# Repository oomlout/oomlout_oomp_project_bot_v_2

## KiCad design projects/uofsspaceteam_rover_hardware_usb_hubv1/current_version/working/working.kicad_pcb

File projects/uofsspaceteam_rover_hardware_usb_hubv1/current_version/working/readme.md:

# rover_hardware
 
## summary 
* id: uofsspaceteam_rover_hardware_usb_hubv1
* user: uofsspaceteam
* name: rover_hardware
* board: usb_hubv1
* repo: https://github.com/UofSSpaceTeam/rover-hardware
* src_file_repo_kicad_pcb: Projects/Power Distribution/TUSB2077A_test_hub/usb_hub.kicad_pcb
* src_file_repo_kicad_pcb_link: https://github.com/UofSSpaceTeam/rover-hardware/tree/master/Projects/Power Distribution/TUSB2077A_test_hub/usb_hub.kicad_pcb
* src_file_repo_kicad_sch: Projects/Power Distribution/DriveController/DriveControllerPower.kicad_sch
* src_file_repo_kicad_sch_link: https://github.com/UofSSpaceTeam/rover-hardware/tree/master/Projects/Power Distribution/DriveController/DriveControllerPower.kicad_sch
* src_file_repo_brd: Projects/Communication/KiCad_USB/modified_eagle_files/RH025.1.brd
* src_file_repo_brd_link: https://github.com/UofSSpaceTeam/rover-hardware/tree/master/Projects/Communication/KiCad_USB/modified_eagle_files/RH025.1.brd
* src_file_repo_sch: Projects/Power Distribution/TUSB2077A_test_hub/usb_hub.sch
* src_file_repo_sch_link: https://github.com/UofSSpaceTeam/rover-hardware/tree/master/Projects/Power Distribution/TUSB2077A_test_hub/usb_hub.sch
* full details link: https://github.com/oomlout/oomlout_oomp_project_bot_v_2/tree/main/projects/uofsspaceteam_rover_hardware_usb_hubv1/current_version/working

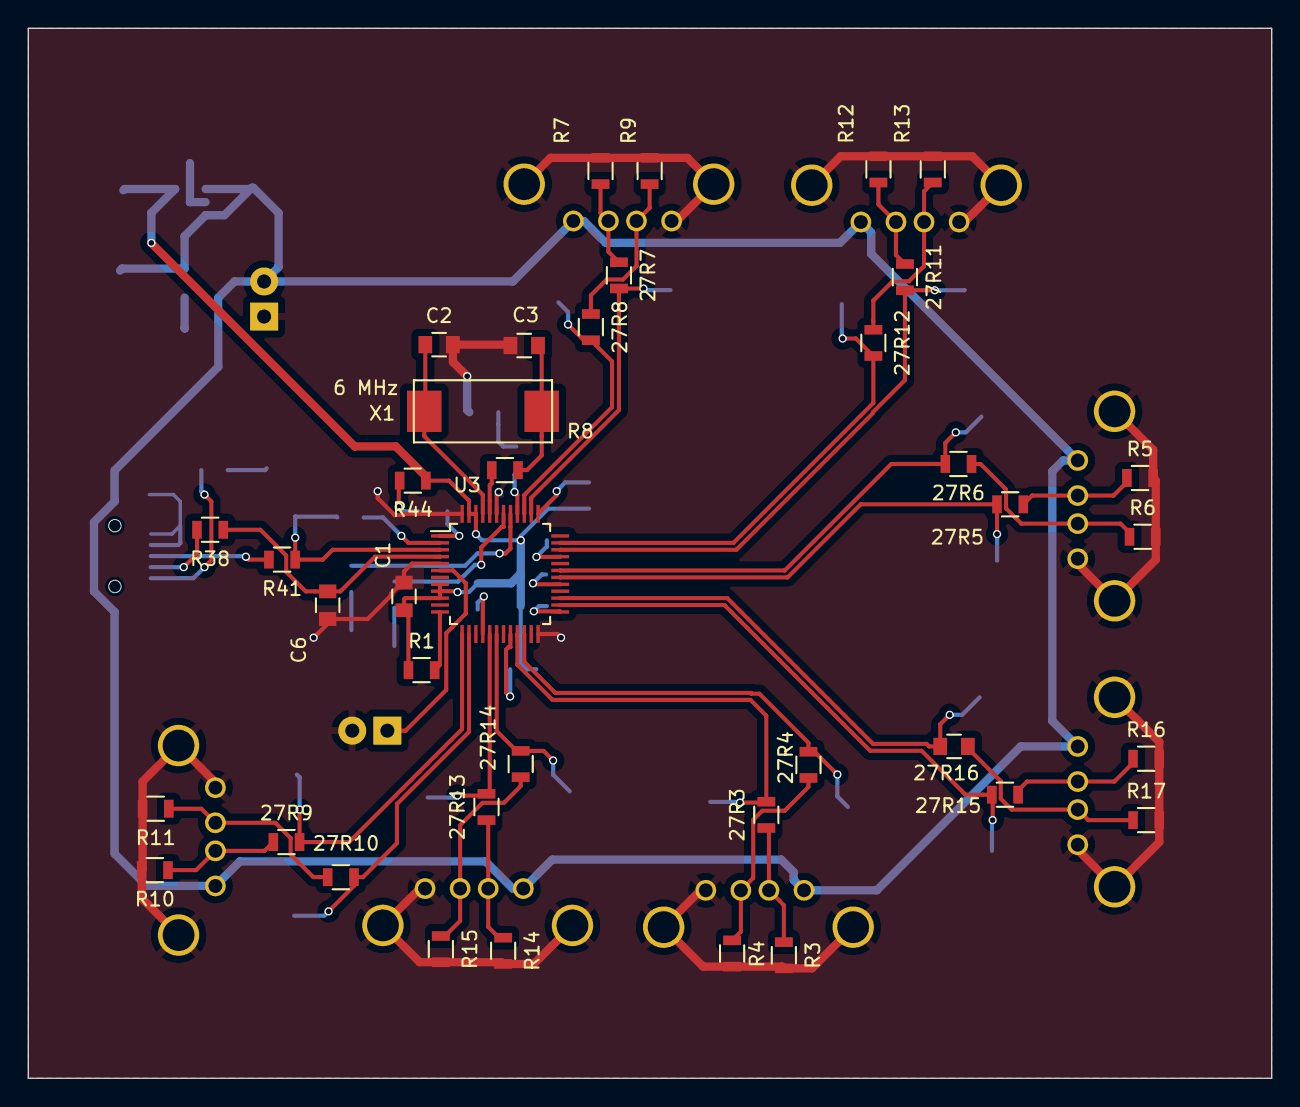
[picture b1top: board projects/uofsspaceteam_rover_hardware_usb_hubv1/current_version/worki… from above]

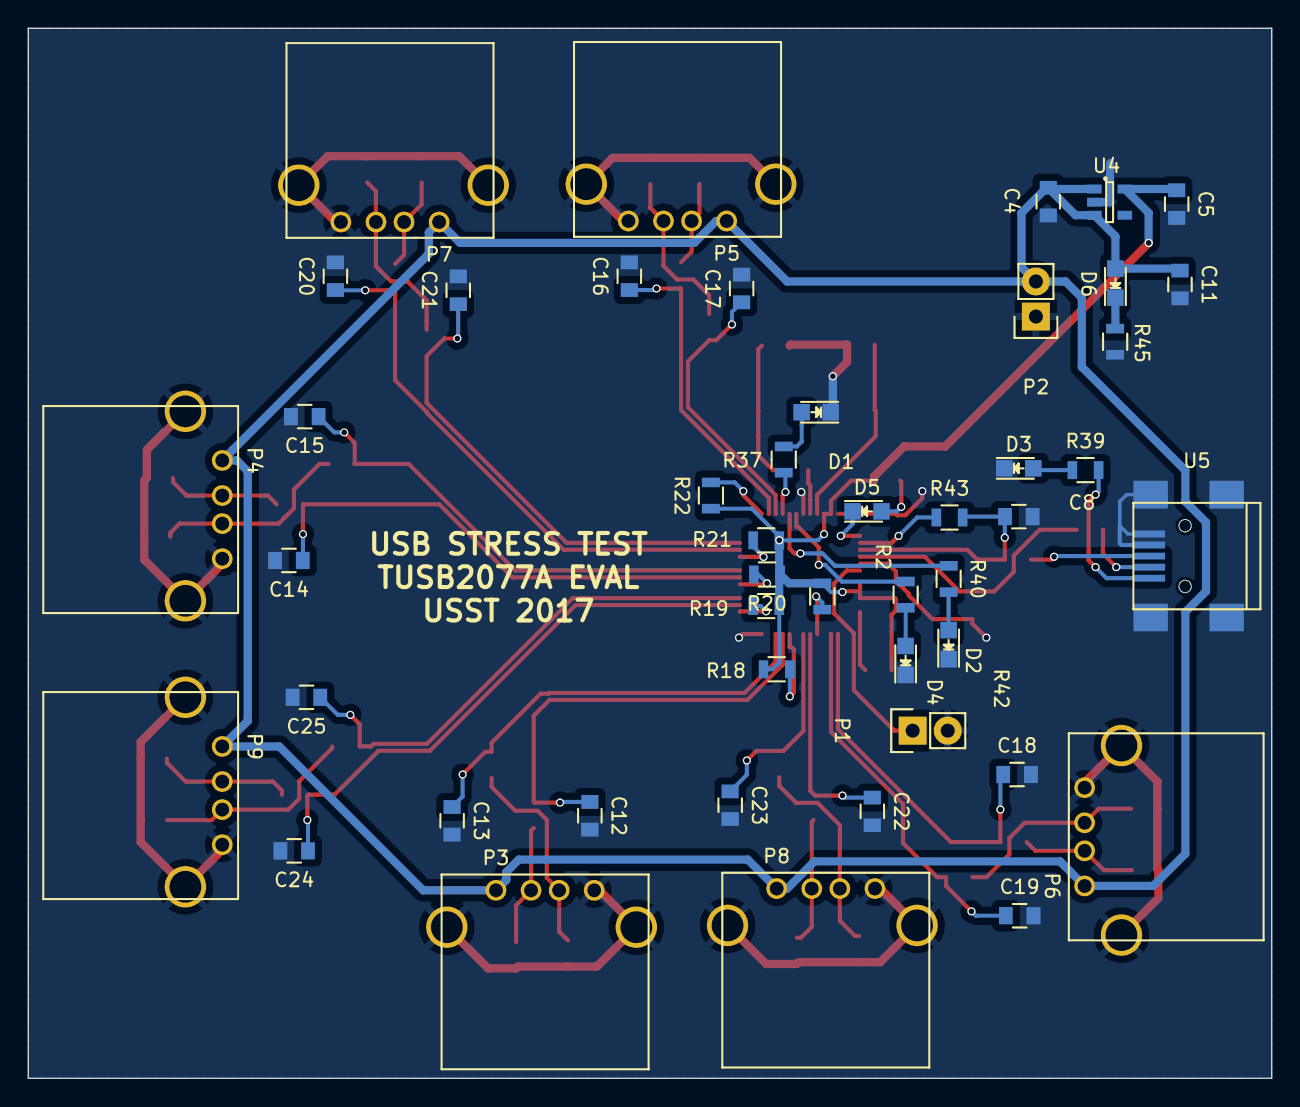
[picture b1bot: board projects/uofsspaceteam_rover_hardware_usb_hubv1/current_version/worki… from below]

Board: 2 copper layers, 90.0 x 76.0 mm, 86 parts (47 on the bottom side), 58 nets.

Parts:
27R3, 27R4, 27R5, 27R6, 27R7, 27R8, 27R9, 27R10, 27R11, 27R12, 27R13, 27R14, 27R15: 27R; R_0805
27R16: 27R; C_0805
C1: 0.1uF; C_0805
C2, C3: 33pF; C_0805
C4: 1uF; C_0805
C5, C11: 10uF; C_0805
C6, C8, C12, C13, C14, C15, C16, C17, C18, C19, C20, C21, C22, C23, C24, C25: 22pF; C_0805
D1, D2, D3, D4, D5, D6: LED; LED_0805
P1: CONN_01X02; Pin_Header_Straight_1x02
P2: CONN_2; Pin_Header_Straight_1x02
P3, P4, P5, P6, P7, P8, P9: USB_A
R1, R2, R3, R4, R5, R6, R7, R9, R10, R11, R12, R13, R14, R15, R16, R17, R18, R19, R20, R21, R22: 15k; R_0805
R8, R43: 1.5k; R_0805
R37, R39, R40, R42, R44, R45: 1k; R_0805
R38, R41: 30; R_0805
U3: TUSB2077A; TQFP-48_7x7mm_Pitch0.5mm
U4: TPS76333; SOT-23-5
U5: USB_A_MALE; USB_Mini-B
X1: 6 MHz; FOX6MHZ

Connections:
+3.3V: C1.1, C5.1, R1.1, R2.1, R18.1, R19.1, R20.1, R21.1, R22.1, R44.1, U3.8, U3.9, U3.10, U3.46, U3.47, U4.5
D0_N: C6.1, R38.1, U3.4
D0_P: C8.1, R41.1, R43.2, U3.3
D1_N: 27R9.2, C18.1, U3.13
D1_P: 27R10.2, C19.1, U3.14
D2_N: 27R13.2, C22.1, U3.17
D2_P: 27R14.2, C23.1, U3.18
D3_N: 27R3.2, C12.1, U3.21
D3_P: 27R4.2, C13.1, U3.22
D4_N: 27R15.2, C24.1, U3.26
D4_P: 27R16.2, C25.1, U3.27
D5_N: 27R5.2, C14.1, U3.30
D5_P: 27R6.2, C15.1, U3.31
D6_N: 27R11.2, C20.1, U3.34
D6_P: 27R12.2, C21.1, U3.35
D7_N: 27R7.2, C16.1, U3.38
D7_P: 27R8.2, C17.1, U3.39
DP0PUR: R43.1, U3.2
GND: C1.2, C2.2, C3.2, C4.2, C5.2, C6.2, C8.2, C11.2, C12.2, C13.2, C14.2, C15.2, C16.2, C17.2, C18.2, C19.2, C20.2, C21.2, C22.2, C23.2, C24.2, C25.2, D1.1, D2.1, D3.1, D4.1, P1.2, P2.1, P3.4, P3.5, P4.4, P4.5, P5.4, P5.5, P6.4, P6.5, P7.4, P7.5, P8.4, P8.5, P9.4, P9.5, R3.2, R4.2, R5.2, R6.2, R7.2, R9.2, R10.2, R11.2, R12.2, R13.2, R14.2, R15.2, R16.2, R17.2, R45.1, U3.5, U3.24, U3.43, U3.48, U4.2, U5.4, U5.5, U5.6
HUBCFG: R37.1, U3.40
unnamed: 27R3.1, P3.2, R3.1
unnamed: 27R4.1, P3.3, R4.1
unnamed: 27R5.1, P4.2, R5.1
unnamed: 27R6.1, P4.3, R6.1
unnamed: 27R7.1, P5.2, R7.1
unnamed: 27R8.1, P5.3, R9.1
unnamed: 27R9.1, P6.2, R10.1
unnamed: 27R10.1, P6.3, R11.1
unnamed: 27R11.1, P7.2, R12.1
unnamed: 27R12.1, P7.3, R13.1
unnamed: 27R13.1, P8.2, R14.1
unnamed: 27R14.1, P8.3, R15.1
unnamed: 27R15.1, P9.2, R16.1
unnamed: 27R16.1, P9.3, R17.1
unnamed: C2.1, U3.45, X1.2
unnamed: C3.1, R8.2, X1.1
unnamed: D1.2, R37.2
unnamed: D2.2, R40.2
unnamed: D3.2, R39.1
unnamed: D4.2, R42.2
unnamed: D5.2, R44.2
unnamed: D6.1, R45.2
unnamed: R1.2, U3.12
unnamed: R2.2, U3.16
unnamed: R8.1, U3.44
unnamed: R18.2, U3.20
unnamed: R19.2, U3.25
unnamed: R20.2, U3.29
unnamed: R21.2, U3.33
unnamed: R22.2, U3.37
unnamed: R38.2, U5.2
unnamed: R39.2, U5.1
unnamed: R41.2, U5.3
PORTDIS: R42.1, U3.42
PORTPWR: R40.1, U3.41
RST: P1.1, U3.6
SPND: D5.1, U3.1
VCC: C4.1, C11.1, D6.2, P2.2, P3.1, P4.1, P5.1, P6.1, P7.1, P8.1, P9.1, U4.1, U4.3

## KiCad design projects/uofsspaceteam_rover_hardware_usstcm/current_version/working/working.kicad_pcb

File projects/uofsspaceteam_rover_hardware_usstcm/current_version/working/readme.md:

# rover_hardware
 
## summary 
* id: uofsspaceteam_rover_hardware_usstcm
* user: uofsspaceteam
* name: rover_hardware
* board: usstcm
* repo: https://github.com/UofSSpaceTeam/rover-hardware
* src_file_repo_kicad_pcb: Projects/USSTCM/USSTCM.kicad_pcb
* src_file_repo_kicad_pcb_link: https://github.com/UofSSpaceTeam/rover-hardware/tree/master/Projects/USSTCM/USSTCM.kicad_pcb
* src_file_repo_kicad_sch: Projects/Power Distribution/DriveController/DriveControllerPower.kicad_sch
* src_file_repo_kicad_sch_link: https://github.com/UofSSpaceTeam/rover-hardware/tree/master/Projects/Power Distribution/DriveController/DriveControllerPower.kicad_sch
* src_file_repo_brd: Projects/Communication/KiCad_USB/modified_eagle_files/RH025.1.brd
* src_file_repo_brd_link: https://github.com/UofSSpaceTeam/rover-hardware/tree/master/Projects/Communication/KiCad_USB/modified_eagle_files/RH025.1.brd
* src_file_repo_sch: Projects/USSTCM/USSTCM.sch
* src_file_repo_sch_link: https://github.com/UofSSpaceTeam/rover-hardware/tree/master/Projects/USSTCM/USSTCM.sch
* full details link: https://github.com/oomlout/oomlout_oomp_project_bot_v_2/tree/main/projects/uofsspaceteam_rover_hardware_usstcm/current_version/working

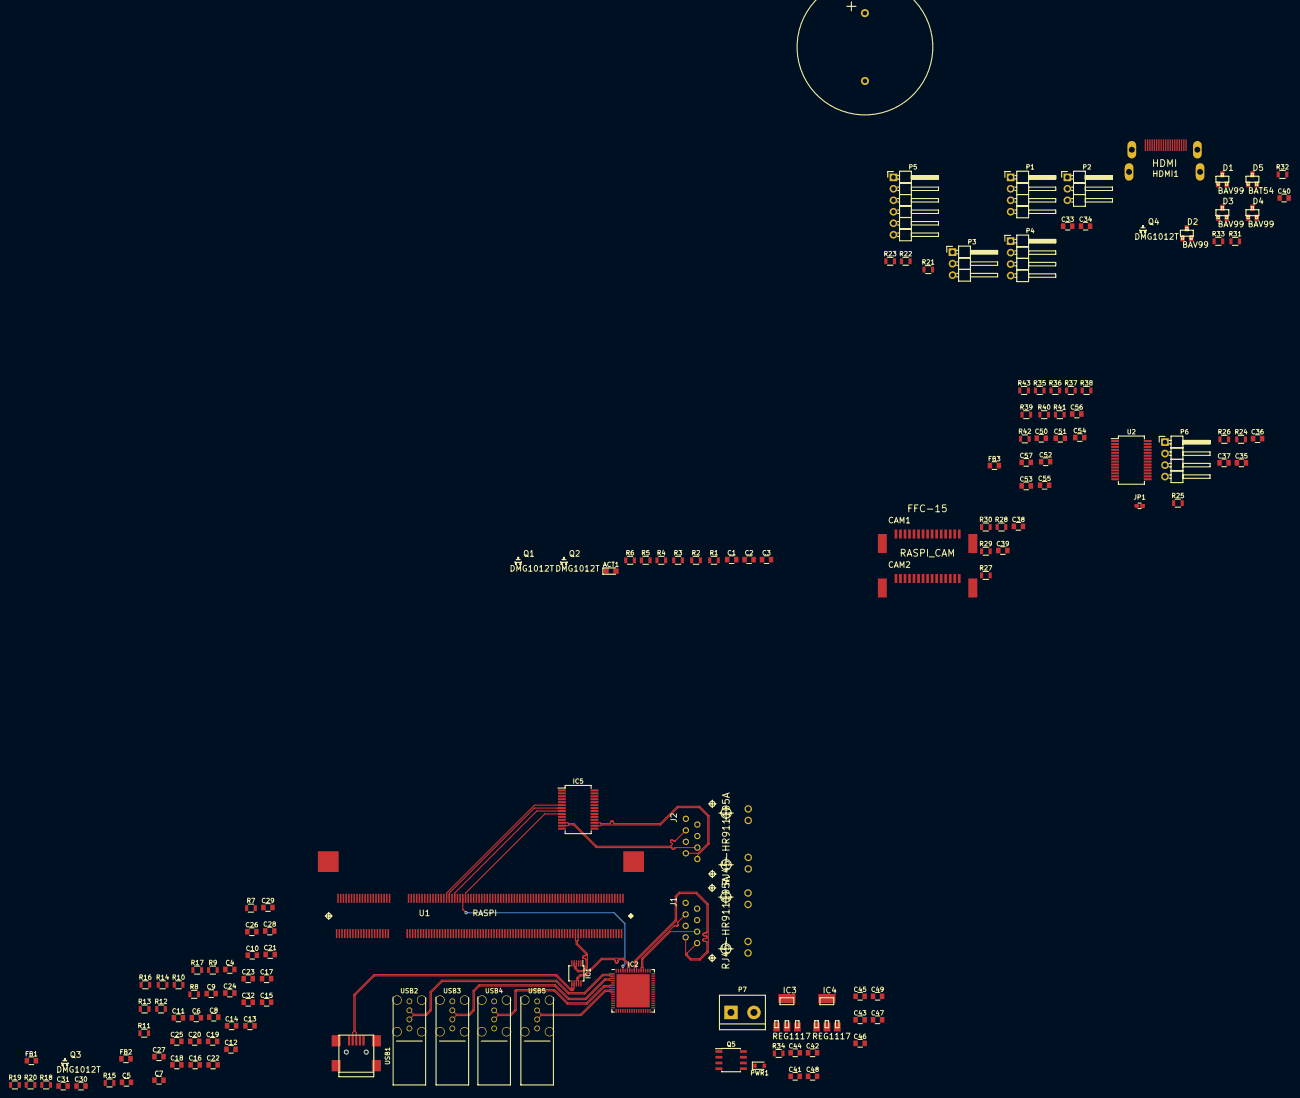
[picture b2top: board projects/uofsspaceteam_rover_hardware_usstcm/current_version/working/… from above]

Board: 4 copper layers, 141 parts (0 on the bottom side), 114 nets.

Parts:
ACT1: LED_0805
C1, C3, C21, C22, C26, C27, C30, C34, C41, C42, C45, C46, C47, C48, C49, C50: 10u; C_0805
C2, C5, C6, C7, C8: 20p; C_0805
C4, C9, C10, C11, C12, C13, C14, C15, C16, C17, C18, C19, C23, C24, C25, C28, C29, C31, C32, C33, C38, C39, C40, C53, C54, C55, C56, C57: 100n; C_0805
C20: 1u; C_0805
C35, C36, C37: 0.1u; C_0805
C43, C44: C_0805
C51, C52: 0.01u; C_0805
CAM1: FFC-15; FFC-15-PICAM
CAM2: RASPI_CAM; FFC-15-PICAM
D1, D2, D3, D4: BAV99; DIODE_SOT23
D5: BAT54; DIODE_SOT23
FB1, FB2: FERRITE_BEAD; C_0805
FB3: 80mA Ferrite; C_0805
HDMI1: HDMI; RASPI_HDMI
IC1: FSUSB42MSOP10; MSOP-10_3x3mm_Pitch0.5mm
IC2: RASPI_LAN9514; QFN-64-1EP_9x9mm_Pitch0.5mm
IC3, IC4: REG1117; BURR-BROWN_SOT223
IC5: ENC28J60; SSOP-28_5.3x10.2mm_Pitch0.65mm
J1, J2: RJ45-HR911105A; HANRUN_RJ45
JP1: Jumper_NC_Small; J_0603
P1: CONN_I2C; Pin_Header_Angled_1x04_Pitch2.54mm
P2: SERVO_PWM0; Pin_Header_Angled_1x03_Pitch2.54mm
P3: SERVO_PWM1; Pin_Header_Angled_1x03_Pitch2.54mm
P4: CONN_UART0; Pin_Header_Angled_1x04_Pitch2.54mm
P5: CONN_UART1_3DR; Pin_Header_Angled_1x06_Pitch2.54mm
P6: CAN_CONN_01X04; Pin_Header_Angled_1x04_Pitch2.54mm
P7: 5V POWER CONN; bornier2
PWR1: D_0805
Q1, Q2, Q3, Q4: DMG1012T; TRANSISTOR-FET_SC75_INFINEON
Q5: FDS6681Z; SOIC-8_3.9x4.9mm_Pitch1.27mm
R1, R2, R3, R26, R33: 100k; R_0805
R4, R5, R9, R10: 47k; R_0805
R6, R22, R23, R27, R28, R29, R30, R31, R32, R34: 1k8; R_0805
R7, R8, R25, R42, R43: 1k; R_0805
R11: 10; R_0805
R12, R13, R14, R15: 49.9; R_0805
R16: 12k4; R_0805
R17, R18, R19, R20: 12k; R_0805
R21: 400; R_0805
R24: 100; R_0805
R35, R36: 10k; R_0805
R37, R38, R40, R41: 50; R_0805
R39: 2.32k; R_0805
SP1: SPEAKER; AI-3035-TWT
U1: RASPI; RASPI_SO-DIMM
U2: MCP25625; SSOP-28_5.3x10.2mm_Pitch0.65mm
USB1: USB-TYPA; MINI-B-USBR
USB2, USB3, USB4, USB5: USB2; USB-A-UPRIGHT

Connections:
+1V8: C43.1, C45.1, C47.1, IC3.2, R5.1, R33.1, U1.183, U1.184, U1.185, U1.186
+3V3: C1.1, C3.1, C4.1, C10.1, C12.1, C23.1, C24.1, C25.1, C31.2, C32.2, C33.2, C35.1, C37.1, C38.2, C39.2, C44.1, C46.1, C48.1, C49.1, C53.1, C54.1, C55.1, C56.1, C57.1, CAM1.15, CAM2.15, FB2.2, FB3.1, IC1.1, IC2.11, IC2.19, IC2.27, IC2.33, IC2.39, IC2.40, IC2.46, IC4.2, IC5.15, IC5.19, IC5.20, IC5.25, IC5.28, P1.1, P4.1, R6.1, R7.1, R8.1, R9.1, R11.2, R12.1, R13.2, R14.2, R15.2, R18.1, R19.2, R20.1, R22.1, R23.2, R26.1, R27.1, R28.1, R29.1, R30.1, R34.1, R35.1, R36.1, U1.39, U1.40, U1.41, U1.42, U1.189, U1.190, U1.191, U1.192, U1.193, U1.194, U2.1, U2.19
+5V: C21.1, C22.1, C26.1, C27.1, C34.2, C36.1, C41.1, C42.1, D5.2, IC3.3, IC4.3, P2.2, P3.2, P5.3, P6.1, Q5.1, Q5.2, Q5.3, R31.1, R32.1, U1.197, U1.198, U1.199, U1.200, U2.27, USB2.VBUS, USB3.VBUS, USB4.VBUS, USB5.VBUS
/CAM0_C_N: CAM1.8, U1.144
/CAM0_C_P: CAM1.9, U1.142
/CAM0_D0_N: CAM1.2, U1.138
/CAM0_D0_P: CAM1.3, U1.136
/CAM0_D1_N: CAM1.5, U1.150
/CAM0_D1_P: CAM1.6, U1.148
/CAM1_C_N: CAM2.8, U1.149
/CAM1_C_P: CAM2.9, U1.147
/CAM1_D0_N: CAM2.2, U1.161
/CAM1_D0_P: CAM2.3, U1.159
/CAM1_D1_N: CAM2.5, U1.155
/CAM1_D1_P: CAM2.6, U1.153
/GPIO0: CAM2.14, R28.2, U1.3
/GPIO1: CAM2.13, R30.2, U1.5
/GPIO5: CAM2.12, U1.17
/GPIO6: IC2.12, R19.1, U1.21
/GPIO8: U1.27, U2.17
/GPIO9: U1.29, U2.16
/GPIO10: U1.33, U2.15
/GPIO11: U1.35, U2.14
/GPIO21: CAM2.11, U1.71
/GPIO25: U1.83, U2.13
/GPIO28: CAM1.14, R3.2, R27.2, U1.28
/GPIO29: CAM1.13, R1.2, R29.2, U1.30
/GPIO30: CAM1.11, U1.34
/GPIO31: CAM1.12, U1.36
/GPIO34: IC5.23, U1.52
/GPIO39: IC5.4, U1.66
/GPIO40: IC5.6, U1.70
/GPIO41: IC5.7, U1.72
/GPIO42: IC5.8, U1.76
/GPIO43: U1.78, U2.9
/GPIO44: IC2.61, R2.2, U1.82
/GPIO45: IC5.9, R35.2, U1.84
/HDMI_CEC: C2.1, D1.3, HDMI1.13, U1.171
/HDMI_CK_N: HDMI1.12, U1.111
/HDMI_CK_P: HDMI1.10, U1.113
/HDMI_D0_N: HDMI1.9, U1.117
/HDMI_D0_P: HDMI1.7, U1.119
/HDMI_D1_N: HDMI1.6, U1.123
/HDMI_D1_P: HDMI1.4, U1.125
/HDMI_D2_N: HDMI1.3, U1.129
/HDMI_D2_P: HDMI1.1, U1.131
/HDMI_SCL: D2.3, HDMI1.15, R32.2, U1.175
/HDMI_SDA: D3.3, HDMI1.16, R31.2, U1.173
/USBD_N: IC1.4, U1.167
/USBD_P: IC1.3, U1.165
/USSTCM CONN/SCL: P1.4, R23.1
/USSTCM CONN/SDA: P1.3, R22.2
/USSTCM LAN/ETH_RX_N: C8.1, IC2.53, J1.6, R12.2
/USSTCM LAN/ETH_RX_P: C7.1, IC2.52, J1.3, R13.1
/USSTCM LAN/ETH_TX_N: C6.1, IC2.56, J1.2, R14.1
/USSTCM LAN/ETH_TX_P: C5.1, IC2.55, J1.1, R15.1
/USSTCM LAN/NLNKA_LED: IC2.21, J1.10
/USSTCM LAN/NSPD_LED: IC2.22, J1.11
/USSTCM LAN/RCT: C9.1, J1.4, J1.5, R11.1
/USSTCM LAN/USB2_N: IC2.1, USB2.D-
/USSTCM LAN/USB2_P: IC2.2, USB2.D+
/USSTCM LAN/USB3_N: IC2.3, USB3.D-
/USSTCM LAN/USB3_P: IC2.4, USB3.D+
/USSTCM LAN/USB4_N: IC2.6, USB4.D-
/USSTCM LAN/USB4_P: IC2.7, USB4.D+
/USSTCM LAN/USB5_N: IC2.8, USB5.D-
/USSTCM LAN/USB5_P: IC2.9, USB5.D+
/USSTCM LAN/USB_BOOT_N: IC1.6, USB1.D-
/USSTCM LAN/USB_BOOT_P: IC1.7, USB1.D+
/USSTCM LAN/USB_LAN_N: IC1.8, IC2.58
/USSTCM LAN/USB_LAN_P: IC1.9, IC2.59
/USSTCM LAN/VDD18CORE: C28.2, C29.2, C30.2, IC2.15, IC2.38
/USSTCM LAN/VDD18PLL: C15.2, FB1.1, IC2.48
/USSTCM_CAN_LITE/CAN_N: P6.3, R24.2, U2.4
/USSTCM_CAN_LITE/CAN_P: JP1.2, P6.4, U2.3
/USSTCM_LAN2/LNKA_LED: IC5.27, J2.9
/USSTCM_LAN2/RCT: C51.1, J2.5, R37.2, R38.1
/USSTCM_LAN2/RD+: IC5.13, J2.3, R37.1
/USSTCM_LAN2/RD-: IC5.12, J2.6, R38.2
/USSTCM_LAN2/SPD_LED: IC5.26, J2.12
/USSTCM_LAN2/TCT: C52.1, FB3.2, J2.4, R40.2, R41.1
/USSTCM_LAN2/TD+: IC5.17, J2.1, R40.1
/USSTCM_LAN2/TD-: IC5.16, J2.2, R41.2
/USSTCM_VIDEO/5V_HDMI: C40.1, D1.2, D2.2, D3.2, D4.2, D5.1, HDMI1.18
/USSTCM_VIDEO/GPIO46: Q4.3, R33.2
/VUSB_BOOT: Q1.1, Q3.1, R4.1, R10.1, USB1.VBUS
GND: C1.2, C2.2, C3.2, C4.2, C5.2, C6.2, C7.2, C8.2, C9.2, C10.2, C11.1, C12.2, C13.1, C14.1, C15.1, C16.1, C17.1, C18.1, C19.1, C20.1, C21.2, C22.2, C23.2, C24.2, C25.2, C26.2, C27.2, C28.1, C29.1, C30.1, C31.1, C32.1, C33.1, C34.1, C35.2, C36.2, C37.2, C38.1, C39.1, C40.2, C41.2, C42.2, C43.2, C44.2, C45.2, C46.2, C47.2, C48.2, C49.2, C50.2, C51.2, C52.2, C53.2, C54.2, C55.2, C56.2, C57.2, CAM1.1, CAM1.4, CAM1.7, CAM1.10, CAM1.16, CAM1.17, CAM2.1, CAM2.4, CAM2.7, CAM2.10, CAM2.16, CAM2.17, D1.1, D2.1, D3.1, D4.1, HDMI1.2, HDMI1.5, HDMI1.8, HDMI1.11, HDMI1.17, HDMI1.P$1, HDMI1.P$2, HDMI1.P$3, HDMI1.P$4, IC1.5, IC1.10, IC2.34, IC2.44, IC2.65, IC3.1, IC4.1, IC5.2, IC5.11, IC5.18, IC5.21, IC5.22, J1.8, J2.8, P1.2, P2.1, P3.1, P4.2, P5.1, P6.2, P7.2, PWR1.1, Q2.2, Q3.2, Q4.2, Q5.4, R1.1, R2.1, R3.1, R4.2, R10.2, R16.1, R17.2, R25.2, R39.2, R42.1, R43.1, SP1.2, U1.1, U1.7, U1.13, U1.19, U1.25, U1.26, U1.31, U1.32, U1.37, U1.38, U1.43, U1.44, U1.49, U1.50, U1.55, U1.56, U1.61, U1.62, U1.67, U1.68, U1.73, U1.74, U1.79, U1.80, U1.85, U1.86, U1.91, U1.92, U1.97, U1.98, U1.103, U1.104, U1.109, U1.110, U1.115, U1.116, U1.121, U1.122, U1.127, U1.133, U1.134, U1.139, U1.140, U1.145, U1.146, U1.151, U1.152, U1.157, U1.163, U1.164, U1.168, U1.169, U1.170, U1.181, U1.182, U1.187, U1.188, U1.195, U1.196, U1.G1, U1.G2, U2.26, USB1.GND, USB2.GND, USB3.GND, USB4.GND, USB5.GND
unnamed: ACT1.1, Q1.2, Q2.3
unnamed: ACT1.2, R6.2
unnamed: C11.2, C14.2, C16.2, C17.2, C18.2, C19.2, FB2.1, IC2.5, IC2.10, IC2.49, IC2.51, IC2.54, IC2.57, IC2.64
unnamed: C20.2, FB1.2, IC2.62
unnamed: C50.1, IC5.1
unnamed: D4.3, HDMI1.19, Q4.1
unnamed: IC1.2, Q3.3, R9.2
unnamed: IC2.28, R20.2
unnamed: IC2.41, R18.2
unnamed: IC2.50, R16.2
unnamed: IC2.63, R17.1
unnamed: IC5.10, R36.2
unnamed: IC5.14, R39.1
unnamed: J1.9, R8.2
unnamed: J1.12, R7.2
unnamed: J2.10, R43.2
unnamed: J2.11, R42.2
unnamed: JP1.1, R24.1
unnamed: P7.1, Q5.5, Q5.6, Q5.7, Q5.8
unnamed: PWR1.2, R34.2
unnamed: Q1.3, U1.2
unnamed: Q2.1, R5.2, U1.90
unnamed: R21.1, SP1.1
unnamed: R25.1, U2.5
unnamed: R26.2, U2.18
unnamed: U2.20, U2.24
unnamed: U2.21, U2.28

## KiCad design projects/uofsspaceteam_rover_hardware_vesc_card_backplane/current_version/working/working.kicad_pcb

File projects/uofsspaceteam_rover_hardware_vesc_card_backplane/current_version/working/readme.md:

# rover_hardware
 
## summary 
* id: uofsspaceteam_rover_hardware_vesc_card_backplane
* user: uofsspaceteam
* name: rover_hardware
* board: vesc_card_backplane
* repo: https://github.com/UofSSpaceTeam/rover-hardware
* src_file_repo_kicad_pcb: Projects/Communication/VESC_Card_Backplane/VESC_Card_Backplane.kicad_pcb
* src_file_repo_kicad_pcb_link: https://github.com/UofSSpaceTeam/rover-hardware/tree/master/Projects/Communication/VESC_Card_Backplane/VESC_Card_Backplane.kicad_pcb
* src_file_repo_kicad_sch: Projects/Communication/VESC_Card_Backplane/CAN_Bus.kicad_sch
* src_file_repo_kicad_sch_link: https://github.com/UofSSpaceTeam/rover-hardware/tree/master/Projects/Communication/VESC_Card_Backplane/CAN_Bus.kicad_sch
* src_file_repo_brd: Projects/Communication/KiCad_USB/modified_eagle_files/RH025.1.brd
* src_file_repo_brd_link: https://github.com/UofSSpaceTeam/rover-hardware/tree/master/Projects/Communication/KiCad_USB/modified_eagle_files/RH025.1.brd
* src_file_repo_sch: Projects/Communication/KiCad_USB/RH025.1.sch
* src_file_repo_sch_link: https://github.com/UofSSpaceTeam/rover-hardware/tree/master/Projects/Communication/KiCad_USB/RH025.1.sch
* full details link: https://github.com/oomlout/oomlout_oomp_project_bot_v_2/tree/main/projects/uofsspaceteam_rover_hardware_vesc_card_backplane/current_version/working

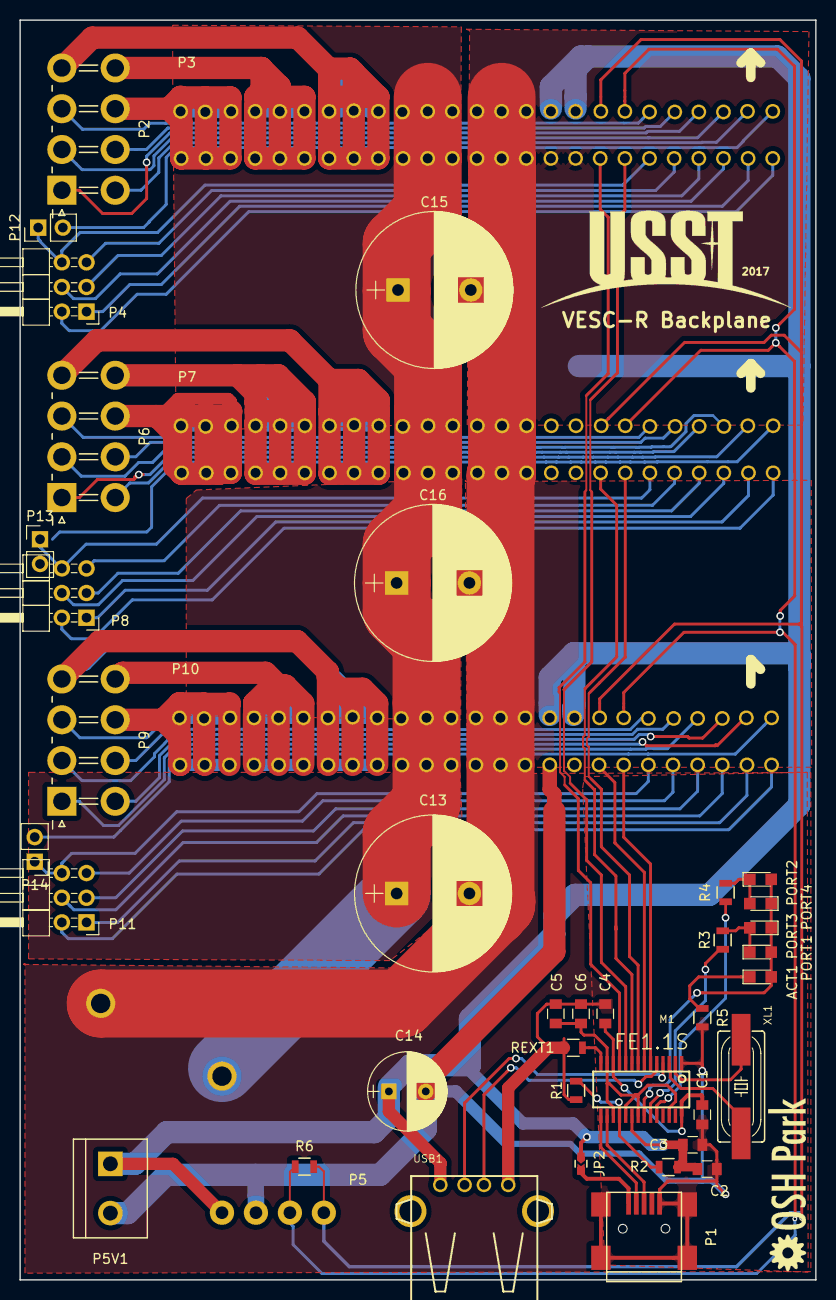
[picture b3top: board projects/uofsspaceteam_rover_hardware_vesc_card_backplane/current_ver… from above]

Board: 2 copper layers, 82.0 x 129.8 mm, 42 parts (1 on the bottom side), 74 nets.

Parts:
ACT1: LED_0805
C1, C2, C5: 10uF; C_0805
C3, C4, C6: 0.1uF; C_0805
C13, C15, C16: 2200u; CP_Radial_D16.0mm_P7.50mm
C14: 100u; CP_Radial_D8.0mm_P3.80mm
JP2: J; J_0603
M1: FE1.1S; FE1.1S_SSOP-28
P1: USB_OTG; USB_Mini-B
P2, P6, P9: EC90_Flat; Molex_MiniFit-JR-5569-08A2_2x04x4.20mm_Angled_Overhang
P3, P7, P10: AMP17614426-2_EDGE; TE2007088-1_Backplane2
P4, P8, P11: CONN_01X06; Pin_Header_Angled_2x03_Pitch2.54mm
P5: CONN_01X04; Molex_39502_1004R
P5V1: CONN_01X02; Molex_39531_1002
P12, P13, P14: CONN_01X02; Pin_Header_Straight_1x02_Pitch2.54mm
PBAT1: CONN_01X02; Phoenix_Contact_PLA5
PORT1, PORT2, PORT3, PORT4: LED_0805
R1: 100K; R_0805
R2: 47K; R_0805
R3, R4, R5: 330; R_0805
R6: 120; R_0805
REXT1: 2.7K; R_0805
USB1: USB-TYPA; USB_A_PTH_AMP787616-1
XL1: 12MHz; HC49UP_SMT_Crystal

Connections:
+5V: C2.1, C3.1, C14.1, JP2.1, M1.20, P3.6, P3.7, P5.1, P5V1.1, P7.6, P7.7, P10.6, P10.7, R2.1, USB1.VBUS
/CANH: P3.8, P5.4, P7.8, P10.8, R6.2
/CAN_Bus/CANL: P3.9, P5.3, P7.9, P10.9, R6.1
/DM_4: M1.4, USB1.D-
/DP_4: M1.5, USB1.D+
/Motor_Controller_A/GND_AUX: P3.21, P4.6, P12.1
/Motor_Controller_A/H1: P2.1, P3.12
/Motor_Controller_A/H2: P2.2, P3.13
/Motor_Controller_A/H3: P2.5, P3.14
/Motor_Controller_A/W: P2.7, P3.1, P3.30
/Motor_Controller_A/X: P2.8, P3.2, P3.29
/Motor_Controller_A/Y: P2.4, P3.3, P3.28
/Motor_Controller_B/GND_AUX: P7.21, P8.6, P13.1
/Motor_Controller_B/H1: P6.1, P7.12
/Motor_Controller_B/H2: P6.2, P7.13
/Motor_Controller_B/H3: P6.5, P7.14
/Motor_Controller_B/W: P6.7, P7.1, P7.30
/Motor_Controller_B/X: P6.8, P7.2, P7.29
/Motor_Controller_B/Y: P6.4, P7.3, P7.28
/Motor_Controller_C/GND_AUX: P10.21, P11.6, P14.1
/Motor_Controller_C/H1: P9.1, P10.12
/Motor_Controller_C/H2: P9.2, P10.13
/Motor_Controller_C/H3: P9.5, P10.14
/Motor_Controller_C/W: P9.7, P10.1, P10.30
/Motor_Controller_C/X: P9.8, P10.2, P10.29
/Motor_Controller_C/Y: P9.4, P10.3, P10.28
/PGND: C13.2, C15.2, C16.2, P3.5, P3.24, P3.25, P3.26, P7.5, P7.24, P7.25, P7.26, P10.5, P10.26, PBAT1.2
/USB_DM_1: M1.10, P3.22
/USB_DM_2: M1.8, P7.22
/USB_DM_3: M1.6, P10.22
/USB_DP_1: M1.11, P3.23
/USB_DP_2: M1.9, P7.23
/USB_DP_3: M1.7, P10.23
/USB_Hub/DM_U: M1.15, P1.2
/USB_Hub/DP_U: M1.16, P1.3
/USB_Hub/N$1: M1.14, REXT1.2
/USB_Hub/N$6: PORT2.1, PORT4.2, R4.2
/USB_Hub/N$7: M1.2, XL1.2
/USB_Hub/N$8: C1.1, C4.1, M1.12, M1.28
/USB_Hub/N$9: M1.3, XL1.1
/USB_Hub/N$13: M1.18, R1.1, R2.2
/USB_Hub/N$20: PORT1.1, PORT3.2, R3.2
/USB_Hub/N$22: ACT1.1, R5.1
/USB_Hub/N$23: M1.23, R3.1
/USB_Hub/N$24: M1.24, R4.1
/USB_Hub/N$25: ACT1.2, M1.22, PORT1.2, PORT2.2, PORT3.1, PORT4.1
/VBAT: C13.1, C15.1, C16.1, P3.4, P3.27, P7.4, P7.27, P10.4, P10.27, PBAT1.1
GND: C1.2, C2.2, C3.2, C4.2, C5.2, C6.2, C14.2, M1.1, P1.5, P1.6, P5.2, P5V1.2, P10.24, P10.25, R1.2, R5.2, REXT1.1, USB1.GND
unnamed: JP2.2, P1.1
unnamed: P2.3, P3.10
unnamed: P2.6, P3.11
unnamed: P3.16, P4.2
unnamed: P3.17, P4.1
unnamed: P3.18, P4.4
unnamed: P3.19, P4.3
unnamed: P3.20, P4.5
unnamed: P6.3, P7.10
unnamed: P6.6, P7.11
unnamed: P7.16, P8.2
unnamed: P7.17, P8.1
unnamed: P7.18, P8.4
unnamed: P7.19, P8.3
unnamed: P7.20, P8.5
unnamed: P9.3, P10.10
unnamed: P9.6, P10.11
unnamed: P10.15, P14.2
unnamed: P10.16, P11.2
unnamed: P10.17, P11.1
unnamed: P10.18, P11.4
unnamed: P10.19, P11.3
unnamed: P10.20, P11.5
unnamed: P3.15, P12.2
unnamed: P7.15, P13.2
VDD: C5.1, C6.1, M1.13, M1.17, M1.19, M1.21, M1.26

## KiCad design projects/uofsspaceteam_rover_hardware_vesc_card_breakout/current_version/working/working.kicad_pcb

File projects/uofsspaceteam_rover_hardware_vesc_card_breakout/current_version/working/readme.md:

# rover_hardware
 
## summary 
* id: uofsspaceteam_rover_hardware_vesc_card_breakout
* user: uofsspaceteam
* name: rover_hardware
* board: vesc_card_breakout
* repo: https://github.com/UofSSpaceTeam/rover-hardware
* src_file_repo_kicad_pcb: Projects/Communication/VESC_Card_Breakout/VESC_Card_Breakout.kicad_pcb
* src_file_repo_kicad_pcb_link: https://github.com/UofSSpaceTeam/rover-hardware/tree/master/Projects/Communication/VESC_Card_Breakout/VESC_Card_Breakout.kicad_pcb
* src_file_repo_kicad_sch: Projects/Communication/VESC_Card_Breakout/Motor_Controller.kicad_sch
* src_file_repo_kicad_sch_link: https://github.com/UofSSpaceTeam/rover-hardware/tree/master/Projects/Communication/VESC_Card_Breakout/Motor_Controller.kicad_sch
* src_file_repo_brd: Projects/Communication/KiCad_USB/modified_eagle_files/RH025.1.brd
* src_file_repo_brd_link: https://github.com/UofSSpaceTeam/rover-hardware/tree/master/Projects/Communication/KiCad_USB/modified_eagle_files/RH025.1.brd
* src_file_repo_sch: Projects/Communication/KiCad_USB/RH025.1.sch
* src_file_repo_sch_link: https://github.com/UofSSpaceTeam/rover-hardware/tree/master/Projects/Communication/KiCad_USB/RH025.1.sch
* full details link: https://github.com/oomlout/oomlout_oomp_project_bot_v_2/tree/main/projects/uofsspaceteam_rover_hardware_vesc_card_breakout/current_version/working

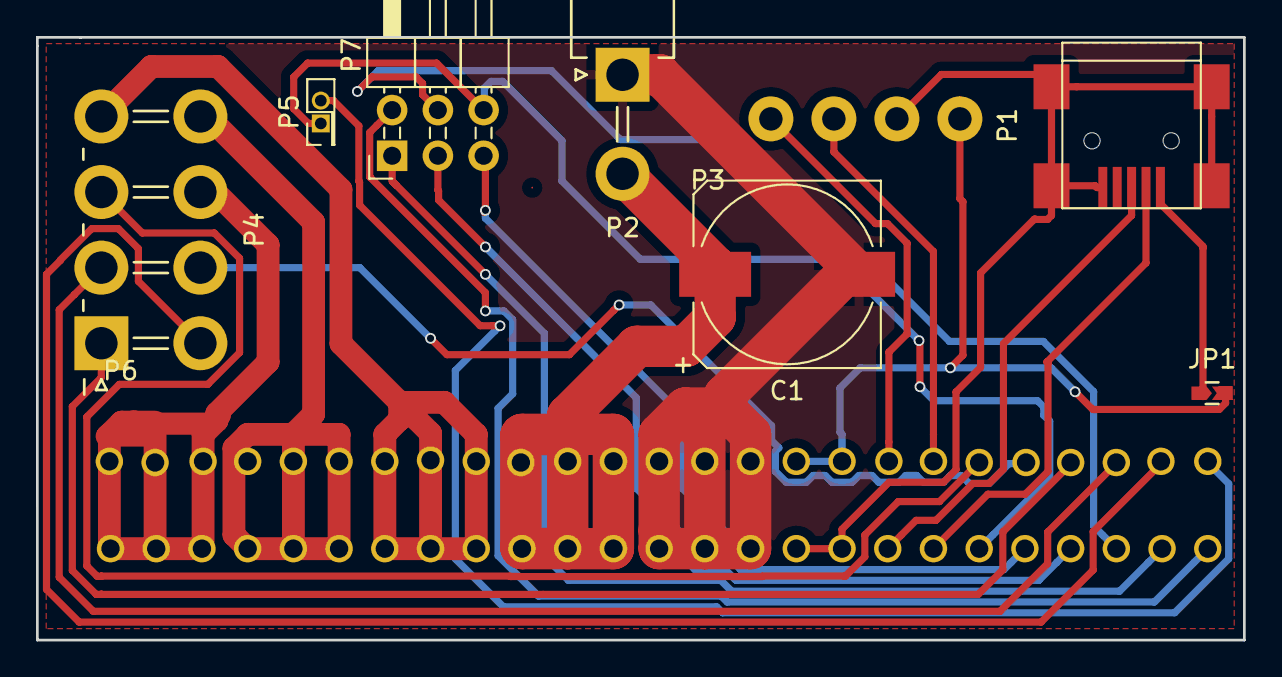
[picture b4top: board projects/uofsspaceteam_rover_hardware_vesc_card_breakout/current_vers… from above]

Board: 2 copper layers, 67.1 x 33.5 mm, 9 parts (0 on the bottom side), 24 nets.

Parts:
C1: CP; CP_Elec_10x10
JP1: Jumper_NO_Small; J_0603
P1: USB_OTG; USB_Mini-B
P2: CONN_01X02; Molex_MiniFit-JR-5569-02A2_2x01x4.20mm_Angled
P3: CONN_01X04; Molex_39502_1004R
P4: EC90_Flat; Molex_MiniFit-JR-5569-08A2_2x04x4.20mm_Angled_Overhang
P5: CONN_01X02; Pin_Header_Straight_2x01_Pitch1.27mm
P6: AMP17614426-2_EDGE; TE2007088-1_Backplane2
P7: CONN_01X06; Pin_Header_Angled_2x03_Pitch2.54mm

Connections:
/5v0: JP1.2, P3.1, P6.6, P6.7
/GNDD: P1.5, P1.6, P3.2, P6.24, P6.25
/Motor_Controller/CANH/TX: P3.4, P6.8
/Motor_Controller/CANL/RX: P3.3, P6.9
/Motor_Controller/GND_AUX: P5.1, P6.21, P7.6
/Motor_Controller/H1: P4.1, P6.12
/Motor_Controller/H2: P4.2, P6.13
/Motor_Controller/H3: P4.5, P6.14
/Motor_Controller/PGND: C1.2, P2.1, P6.5, P6.26
/Motor_Controller/USBDM: P1.2, P6.22
/Motor_Controller/USBDP: P1.3, P6.23
/Motor_Controller/VBAT: C1.1, P2.2, P6.4, P6.27
/Motor_Controller/W: P4.7, P6.1, P6.30
/Motor_Controller/X: P4.8, P6.2, P6.29
/Motor_Controller/Y: P4.4, P6.3, P6.28
unnamed: JP1.1, P1.1
unnamed: P4.3, P6.10
unnamed: P4.6, P6.11
unnamed: P5.2, P6.15
unnamed: P6.16, P7.2
unnamed: P6.17, P7.1
unnamed: P6.18, P7.4
unnamed: P6.19, P7.3
unnamed: P6.20, P7.5

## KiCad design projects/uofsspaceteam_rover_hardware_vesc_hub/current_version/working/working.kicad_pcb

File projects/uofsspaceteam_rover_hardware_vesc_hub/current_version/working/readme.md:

# rover_hardware
 
## summary 
* id: uofsspaceteam_rover_hardware_vesc_hub
* user: uofsspaceteam
* name: rover_hardware
* board: vesc_hub
* repo: https://github.com/UofSSpaceTeam/rover-hardware
* src_file_repo_kicad_pcb: Projects/Communication/VESC_Hub/VESC_Hub.kicad_pcb
* src_file_repo_kicad_pcb_link: https://github.com/UofSSpaceTeam/rover-hardware/tree/master/Projects/Communication/VESC_Hub/VESC_Hub.kicad_pcb
* src_file_repo_kicad_sch: Projects/Communication/VESC_Hub/USB_Hub.kicad_sch
* src_file_repo_kicad_sch_link: https://github.com/UofSSpaceTeam/rover-hardware/tree/master/Projects/Communication/VESC_Hub/USB_Hub.kicad_sch
* src_file_repo_brd: Projects/Communication/KiCad_USB/modified_eagle_files/RH025.1.brd
* src_file_repo_brd_link: https://github.com/UofSSpaceTeam/rover-hardware/tree/master/Projects/Communication/KiCad_USB/modified_eagle_files/RH025.1.brd
* src_file_repo_sch: Projects/Communication/KiCad_USB/RH025.1.sch
* src_file_repo_sch_link: https://github.com/UofSSpaceTeam/rover-hardware/tree/master/Projects/Communication/KiCad_USB/RH025.1.sch
* full details link: https://github.com/oomlout/oomlout_oomp_project_bot_v_2/tree/main/projects/uofsspaceteam_rover_hardware_vesc_hub/current_version/working

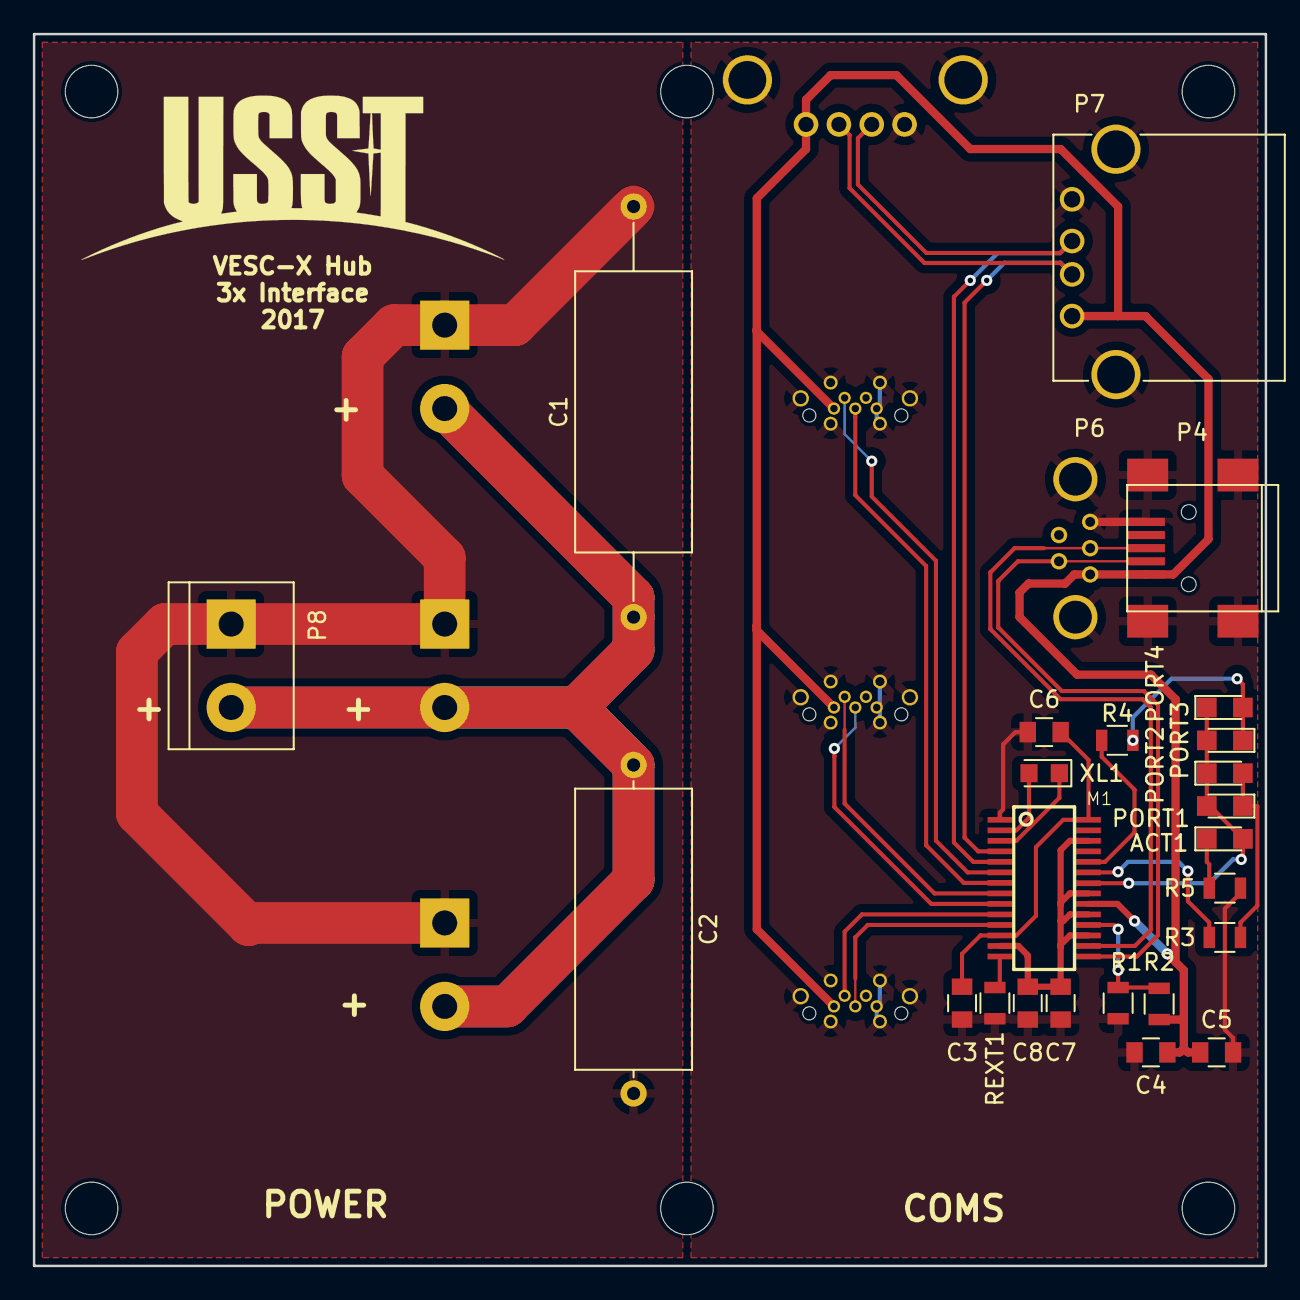
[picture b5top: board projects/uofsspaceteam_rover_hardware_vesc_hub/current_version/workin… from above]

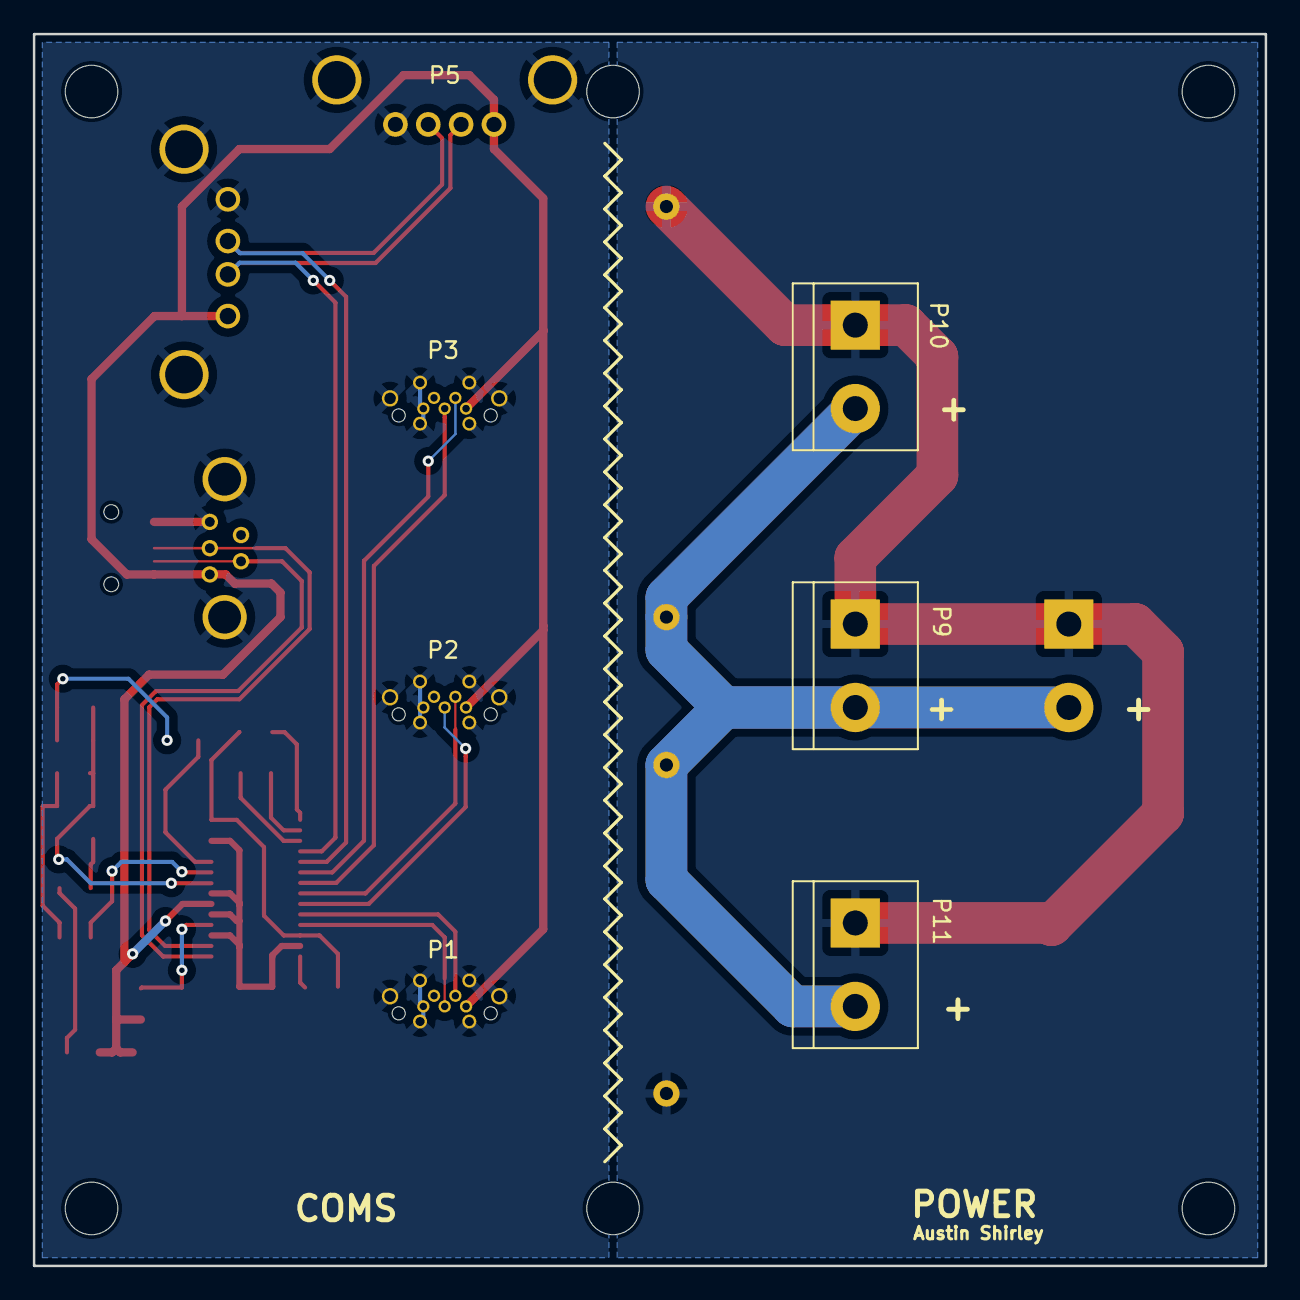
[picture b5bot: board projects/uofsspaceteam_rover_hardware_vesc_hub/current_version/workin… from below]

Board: 2 copper layers, 75.0 x 75.0 mm, 32 parts (7 on the bottom side), 26 nets.

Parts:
ACT1: LED_0805
C1: 2000u; C_Axial_L17.0mm_D7.0mm_P25.00mm_Horizontal
C2: 2000u; C_Axial_L17.0mm_D7.0mm_P20.00mm_Horizontal
C3, C4, C7: 10uF; C_0805
C5, C6, C8: 0.1uF; C_0805
M1: FE1.1S; FE1.1S_SSOP-28
P1: USB_OTG_M1; USB3150_Micro_Vertical
P2: USB_OTG_M2; USB3150_Micro_Vertical
P3: USB_OTG_M3; USB3150_Micro_Vertical
P4: USB_OTG_UP; USB_Mini-B
P5: USB_DS; WRCOM_USB_A_VERT
P6: USB_OTG_UP; WRCOM_MINI_USB_VERT
P7: USB_DS; USB_A
P8: POWER_IN; bornier2
P9: M1; bornier2
P10: M2; bornier2
P11: M3; bornier2
PORT1, PORT2, PORT3, PORT4: LED_0805
R1: 100K; R_0805
R2: 47K; R_0805
R3, R4, R5: 330; R_0805
REXT1: 2.7K; R_0805
XL1: 12MHz; Crystal_SMD_2012-2pin_2.0x1.2mm_HandSoldering

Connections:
+5V: C4.1, C5.1, M1.20, P1.1, P2.1, P3.1, P4.1, P5.1, P6.1, P7.1, R2.1
+24V: C1.1, C2.1, P8.2, P9.2, P10.2, P11.2
/USB1_N: M1.4, P5.2, P7.2
/USB1_P: M1.5, P5.3, P7.3
/USB2_N: M1.6, P3.2
/USB2_P: M1.7, P3.3
/USB3_N: M1.8, P2.2
/USB3_P: M1.9, P2.3
/USB4_N: M1.10, P1.2
/USB4_P: M1.11, P1.3
/USBUP_N: M1.15, P4.2, P6.2
/USBUP_P: M1.16, P4.3, P6.3
GND: C1.2, C2.2, P8.1, P9.1, P10.1, P11.1
GNDD: C3.2, C4.2, C5.2, C6.2, C7.2, C8.2, M1.1, P1.5, P1.6, P2.5, P2.6, P3.5, P3.6, P4.5, P4.6, P5.4, P5.5, P6.5, P6.6, P7.4, P7.5, R1.2, R5.2, REXT1.1
unnamed: ACT1.1, R5.1
unnamed: ACT1.2, M1.22, PORT1.2, PORT2.1, PORT3.2, PORT4.1
unnamed: C3.1, C6.1, M1.12, M1.28
unnamed: M1.2, XL1.2
unnamed: M1.3, XL1.1
unnamed: M1.14, REXT1.2
unnamed: M1.18, R1.1, R2.2
unnamed: M1.23, R3.1
unnamed: M1.24, R4.1
unnamed: PORT1.1, PORT2.2, R3.2
unnamed: PORT3.1, PORT4.2, R4.2
VDD: C7.1, C8.1, M1.13, M1.17, M1.19, M1.21, M1.26
